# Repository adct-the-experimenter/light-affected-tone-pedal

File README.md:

# Light-Affected Tone Pedal

This is an analog circuit and pcb for the product Light-Affected Tone pedal designed by Another Dimension Effects.

## Simulation
- Web Demo: adfxz.com/light-affected-tone-pedal
- Circuit: light-tone-pedal-circuit.asc

The Light Dependent Resistors used range from 3k ohms to 11k ohms.

## Key Components

- The dual op-amp used is LM358AP.

- Advanced Photonix PDV-8001 LDR https://www.digikey.com/product-detail/en/advanced-photonix/PDV-P8001/PDV-P8001-ND/480602

## Why PWM should not be used

The light-dependent resistor is very sensitive to big changes in light. 
It will pick up the LED turning on and off very quickly and produce high frequency noise close to the flashing frequency of the LED.
Low-pass filter is recommended for use with PWM signals.

## What you can do with the circuit
You are free to copy, modify, sell, or use this circuit in derived works as long as you include the conditions of the license 
and copyright notice with the product. 

If you are selling a product using this circuit or a modified version of it, 
you must include a slip of paper that contains the license conditions and copyright to Another Dimension Effects and Pablo Antinio Camacho Jr.

Read License.txt for details.

##Important Note
Do not place the light dependent resistor or LED(light-emitting diode) on the board.
Instead place the components in a separate board and and connect the leads/terminals to the pcb.

## Warning

Do not mass produce and sell this pedal without FCC compliance in the United States of America.
The same restriction applies to other countries with government bodies concerned with regulation of electro-magnetic interference.

Another Dimension Effects and/or Pablo Antonio Camacho Jr. are not liable for any damage caused by this pedal including EMI.

## Sponsors
The completion of the project is being sponsored by PCBWay.

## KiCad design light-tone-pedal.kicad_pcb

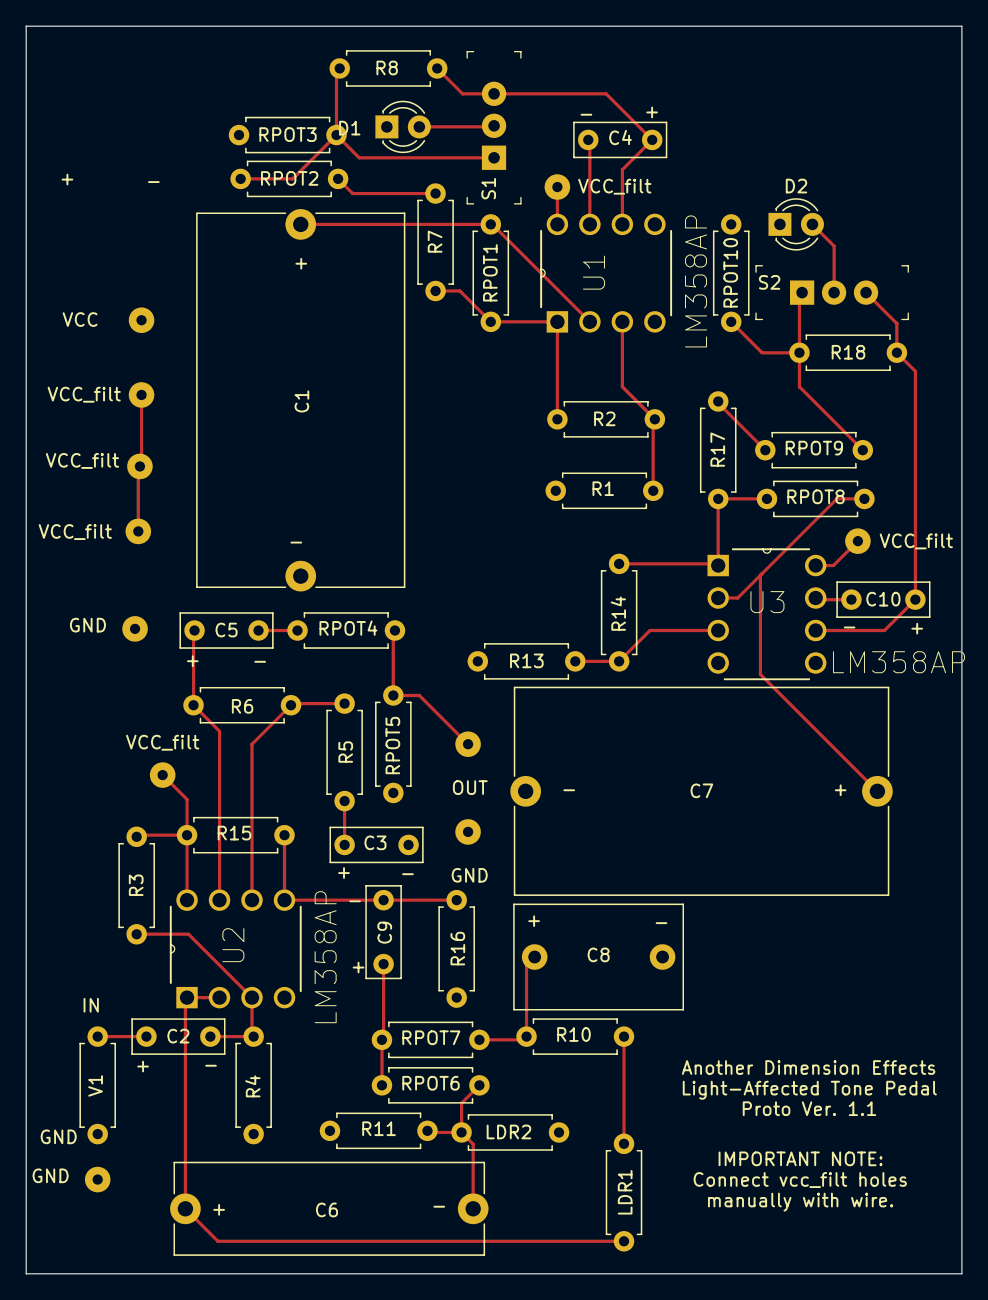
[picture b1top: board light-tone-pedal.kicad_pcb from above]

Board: 2 copper layers, 73.2 x 97.5 mm, 57 parts (0 on the bottom side), 31 nets.

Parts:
C1, C7: 2u; C_Rect_L29.0mm_W16.0mm_P27.50mm_MKT
C2, C3: 0.1u; C_Disc_D7.0mm_W2.5mm_P5.00mm
C4, C10: 1u; C_Disc_D7.0mm_W2.5mm_P5.00mm
C5, C9: 10u; C_Disc_D7.0mm_W2.5mm_P5.00mm
C6: 5600p; C_Rect_L24.0mm_W7.0mm_P22.50mm_MKT
C8: 0.022u; C_Rect_L13.0mm_W8.0mm_P10.00mm_FKS3_FKP3_MKS4
D1, D2: CQY99; LED_D3.0mm
GND: SolderWirePad_1x01_Drill0.8mm
GND#2, GND#3: SolderWirePad_1x01_Drill0.8mm
LDR1, LDR2: RLDR3k-11k; R_Axial_DIN0207_L6.3mm_D2.5mm_P7.62mm_Horizontal
OUT: SolderWirePad_1x01_Drill0.8mm
R1, R3, R4, R13, R15, R16: 1Meg; R_Axial_DIN0207_L6.3mm_D2.5mm_P7.62mm_Horizontal
R2, R5, R14: 1k; R_Axial_DIN0207_L6.3mm_D2.5mm_P7.62mm_Horizontal
R6: 100k; R_Axial_DIN0207_L6.3mm_D2.5mm_P7.62mm_Horizontal
R7, R17: 10k; R_Axial_DIN0207_L6.3mm_D2.5mm_P7.62mm_Horizontal
R8, R18: 120k; R_Axial_DIN0207_L6.3mm_D2.5mm_P7.62mm_Horizontal
R10, R11: 24k; R_Axial_DIN0207_L6.3mm_D2.5mm_P7.62mm_Horizontal
RPOT1, RPOT8: R20kLin; R_Axial_DIN0207_L6.3mm_D2.5mm_P7.62mm_Horizontal
RPOT2, RPOT3, RPOT9, RPOT10: R10kLin; R_Axial_DIN0207_L6.3mm_D2.5mm_P7.62mm_Horizontal
RPOT4, RPOT5: R1MegLog; R_Axial_DIN0207_L6.3mm_D2.5mm_P7.62mm_Horizontal
RPOT6, RPOT7: R100kLin; R_Axial_DIN0207_L6.3mm_D2.5mm_P7.62mm_Horizontal
S1, S2: EG1218; Switch_Slide_11.6x4mm_EG1218
U1, U2, U3: LM358AP; DIP254P762X508-8
V1: VSOURCE; R_Axial_DIN0207_L6.3mm_D2.5mm_P7.62mm_Horizontal
VCC: SolderWirePad_1x01_Drill0.8mm
VCC_filt: SolderWirePad_1x01_Drill0.8mm
VCC_filt#2, VCC_filt#3, VCC_filt#4, VCC_filt#5, VCC_filt#6: SolderWirePad_1x01_Drill0.8mm

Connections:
GND: C1.2, C3.2, C7.2, C8.2, D1.1, D2.1, GND.1, GND#2.1, GND#3.1, LDR2.1, R1.1, R4.2, R11.1, R13.1, R16.2, RPOT3.2, RPOT5.2, RPOT10.2, U1.4, U1.5, U2.4, U3.4, U3.5, V1.2
unnamed: C1.1, RPOT1.2, U1.2
unnamed: C2.2, R3.2, R4.1, U2.3
unnamed: C3.1, R5.2
unnamed: C4.1, U1.7
unnamed: C5.1, R6.2, U2.7
unnamed: C5.2, RPOT4.1
unnamed: C6.1, LDR2.2, R11.2, RPOT6.1
unnamed: C6.2, LDR1.1, U2.1, U2.2
unnamed: C7.1, RPOT8.2, U3.2
unnamed: C8.1, R10.1, RPOT7.2
unnamed: C9.1, R15.2, R16.1, U2.5
unnamed: C9.2, RPOT6.2, RPOT7.1
unnamed: C10.1, U3.7
unnamed: LDR1.2, R10.2
unnamed: R1.2, R2.2, U1.3
unnamed: R2.1, R7.2, RPOT1.1, U1.1
unnamed: R5.1, R6.1, U2.6
unnamed: R7.1, RPOT2.1
unnamed: R13.2, R14.2, U3.3
unnamed: R14.1, R17.2, RPOT8.1, U3.1
unnamed: R17.1, RPOT9.1
Out1: D1.2, S1.2
Out2: D2.2, S2.2
Square1: R8.1, RPOT2.2, RPOT3.1, S1.1
Square2: R18.1, RPOT9.2, RPOT10.1, S2.1
Triangle1: C4.2, R8.2, S1.3, U1.6
Triangle2: C10.2, R18.2, S2.3, U3.6
vcc_filtered: R3.1, R15.1, U1.8, U2.8, U3.8, VCC_filt.1, VCC_filt#2.1, VCC_filt#3.1, VCC_filt#4.1, VCC_filt#5.1, VCC_filt#6.1
vin: C2.1, V1.1
vout: OUT.1, RPOT4.2, RPOT5.1

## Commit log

2019-05-24 Added pciture of drawn schematic circuit to repo for reference and clarification.
2019-05-24 Removed large .png file and replaced it with a pdf of circuit.
2019-05-25 Started tracking this project.
2019-05-25 Completed schematic of circuit in use for light-affected tone pedal.
2019-05-25 Added Another Dimension Effects business as copyright owner in LICENSE.txt
2019-05-25 Added LTSPICE circuit simulation
2019-05-25 Update LICENSE.txt
    Made a correction for it to apply to hardware.
2019-05-26 Fixed a mistake. Had wrong value for C1.
2019-05-30 Added .gitignore file
2019-05-30 Updated LFO Square wave circuit.
2019-05-30 Made LFO square and triangle wave circuit to flash light to LEDs.
2019-06-03 Improved the triangle wave to have closer amplitude in voltage to that of the square wave.
2019-06-04 Updated the circuit for light tone pedal to make it have more effect in low tones.
2019-06-04 Improved light affected tone pedal to have more effect in the low tones.
2019-06-05 Added pwr_flag symbol to schematic in eeschema.
2019-06-07 Added switch and signal generators. Also made pcb.
2019-06-13 Updated pdf of circuit schematic. Made pcb for light affected tone pedal.
2019-09-16 Added Bill of Materials.
2019-10-03 Added sponsor acknowledgment.
2019-11-03 Updated README.md with important information and progress of project.
2019-12-09 Added a low pass filter to power of circuit to take out noise from power supply.
2019-12-09 Removed gerber directory and .zip file so it would be safer for everyone to generate and check their own gerber files.
2019-12-09 Removed unused file.
2020-01-18 Updated README links.
2020-01-25 Added polarity symbols on pcb for capacitors for the case of when polarized capacitors are used.
2020-02-01 Updated README.md with important note.
2020-02-15 I removed the low-pass filter since it was not working out too well in pcb design.
2022-06-12 Improved gain and bias of op amp configurations. Need to make it stable.
2022-06-12 Improved gain, phase, output impedance and circuit overall.
2022-06-12 Changed BOM name.
2022-06-12 Cleanup
2022-06-14 More cleanup. Also reorganization.
2022-06-14 Cleanup. Reorganization.
2022-06-14 Cleanup.
2022-06-14 Reorganizing files.
2022-06-14 Reorganized files.
2022-06-15 Changed README.md
